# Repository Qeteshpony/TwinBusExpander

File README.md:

# TwinBusExpander

[Hardware Documentation](https://qeteshpony.github.io/TwinBusExpander)

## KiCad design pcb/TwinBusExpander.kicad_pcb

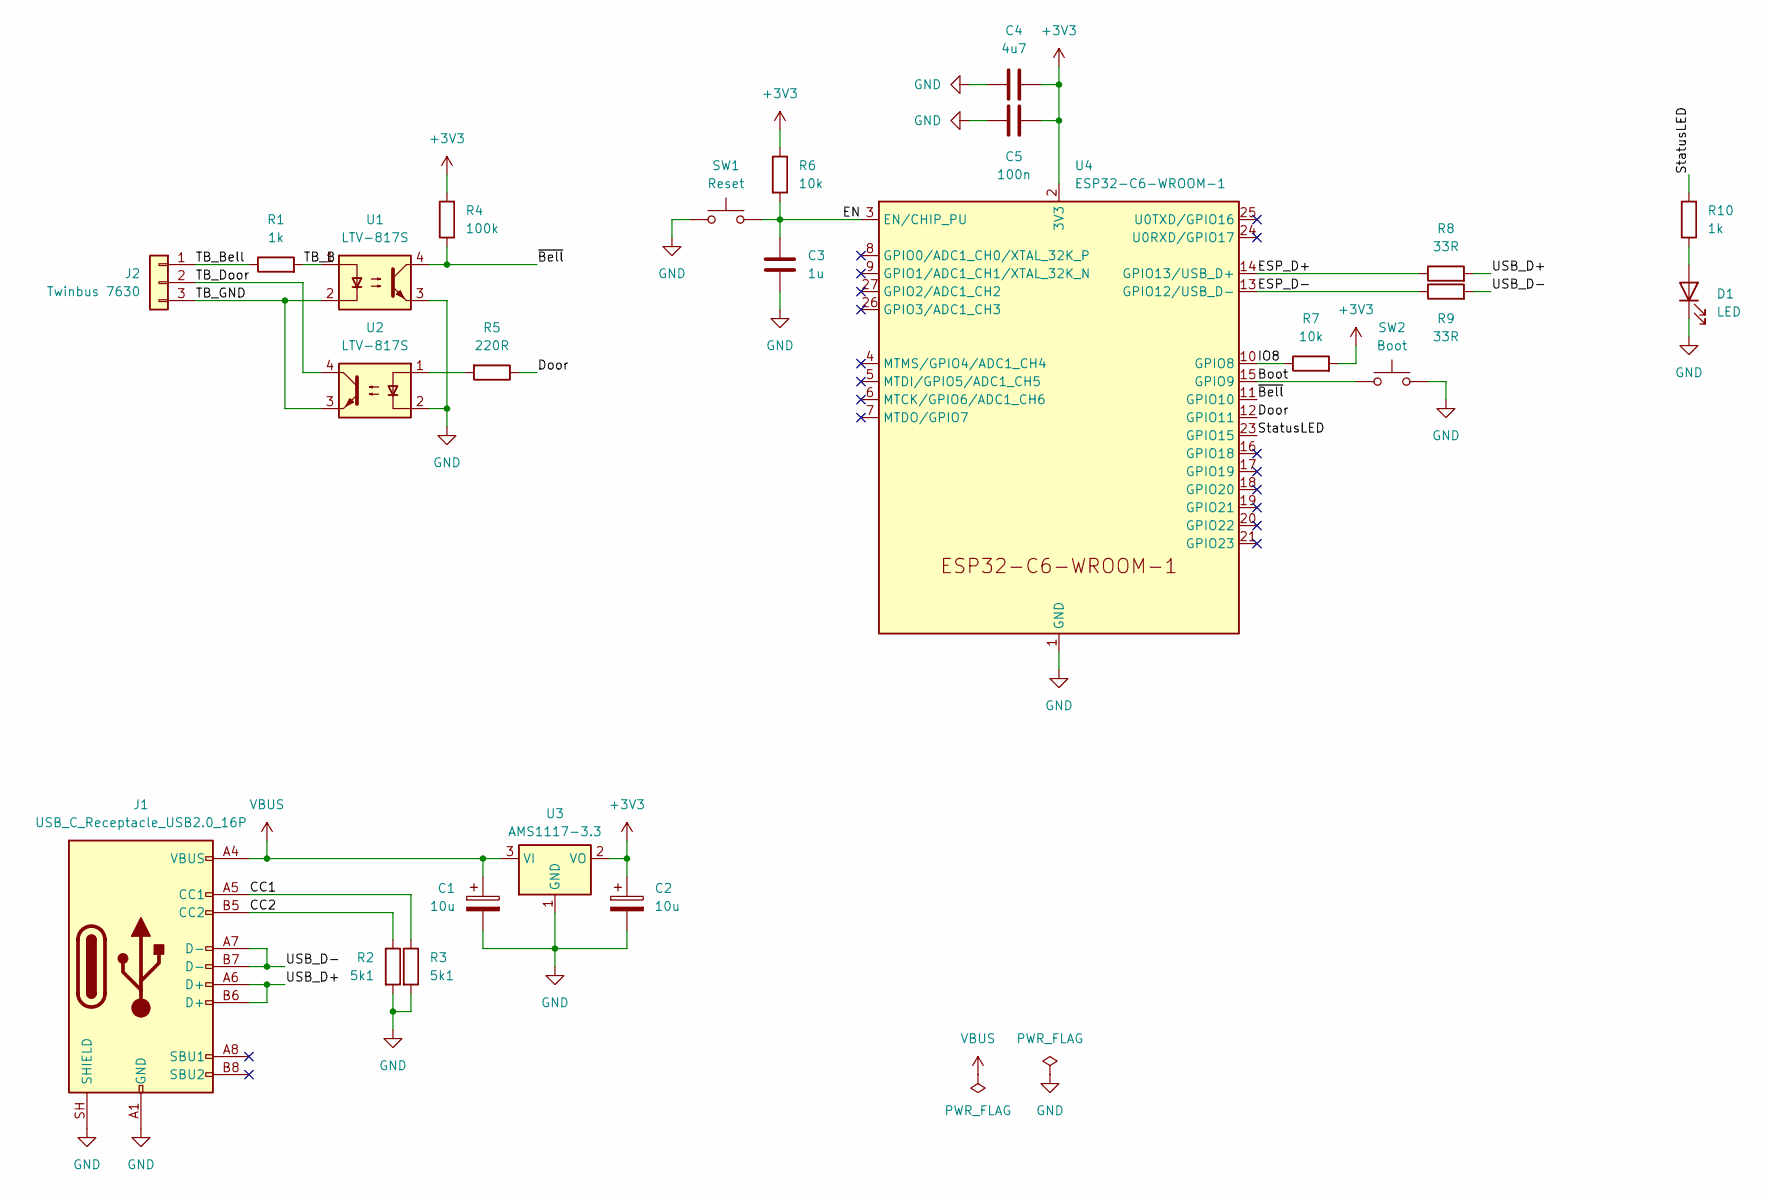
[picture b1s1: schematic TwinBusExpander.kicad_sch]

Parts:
C1, C2: 10u; CP_EIA-3216-18_Kemet-A; LCSC C7171
C3: 1u; C_0402_1005Metric; LCSC C52923
C4: 4u7; C_0402_1005Metric; LCSC C23733
C5: 100n; C_0402_1005Metric; LCSC C1525
D1: LED; LED_0603_1608Metric; LCSC C2286
J1: USB_C_Receptacle_USB2.0_16P; USB_C_Receptacle_GCT_USB4105-xx-A_16P_TopMnt_Horizontal; LCSC C393939
J2: Twinbus 7630; JST_PH_S3B-PH-K_1x03_P2.00mm_Horizontal; LCSC C157929
R1, R10: 1k; R_0402_1005Metric; LCSC C11702
R2, R3: 5k1; R_0402_1005Metric; LCSC C25905
R4: 100k; R_0402_1005Metric; LCSC C25741
R5: 220R; R_0402_1005Metric; LCSC C25091
R6, R7: 10k; R_0402_1005Metric; LCSC C25744
R8, R9: 33R; R_0402_1005Metric; LCSC C25105
SW1: Reset; SW_SPST_TS-1088-xR020; LCSC C720477
SW2: Boot; SW_SPST_TS-1088-xR020; LCSC C720477
U1, U2: LTV-817S; SMDIP-4_W9.53mm; LCSC C109227
U3: AMS1117-3.3; SOT-223-3_TabPin2; LCSC C6186
U4: ESP32-C6-WROOM-1

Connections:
+3V3: C2.1, C4.2, C5.2, R4.2, R6.1, R7.2, U3.2 (VO), U4.2 (3V3)
/Boot: SW2.1, U4.15 (GPIO9)
/CC1: J1.A5 (CC1), R3.1
/CC2: J1.B5 (CC2), R2.1
/Door: R5.1, U4.12 (GPIO11)
/EN: C3.1, R6.2, SW1.2, U4.3 (EN/CHIP_PU)
/ESP_D+: R8.1, U4.14 (GPIO13/USB_D+)
/ESP_D-: R9.1, U4.13 (GPIO12/USB_D-)
/IO8: R7.1, U4.10 (GPIO8)
/StatusLED: R10.2, U4.23 (GPIO15)
/TB_B: R1.2, U1.1
/TB_Bell: J2.1, R1.1
/TB_Door: J2.2, U2.4
/TB_GND: J2.3, U1.2, U2.3
/USB_D+: J1.A6 (D+), J1.B6 (D+), R8.2
/USB_D-: J1.A7 (D-), J1.B7 (D-), R9.2
/~Bell: R4.1, U1.4, U4.11 (GPIO10)
GND: C1.2, C2.2, C3.2, C4.1, C5.1, D1.1 (K), J1.A1 (GND), J1.A12 (GND), J1.B1 (GND), J1.B12 (GND), J1.SH (SHIELD), R2.2, R3.2, SW1.1, SW2.2, U1.3, U2.2, U3.1 (GND), U4.1 (GND), U4.28 (GND), U4.29 (GND)
unnamed: D1.2 (A), R10.1
unnamed: R5.2, U2.1
VBUS: C1.1, J1.A4 (VBUS), J1.A9 (VBUS), J1.B4 (VBUS), J1.B9 (VBUS), U3.3 (VI)

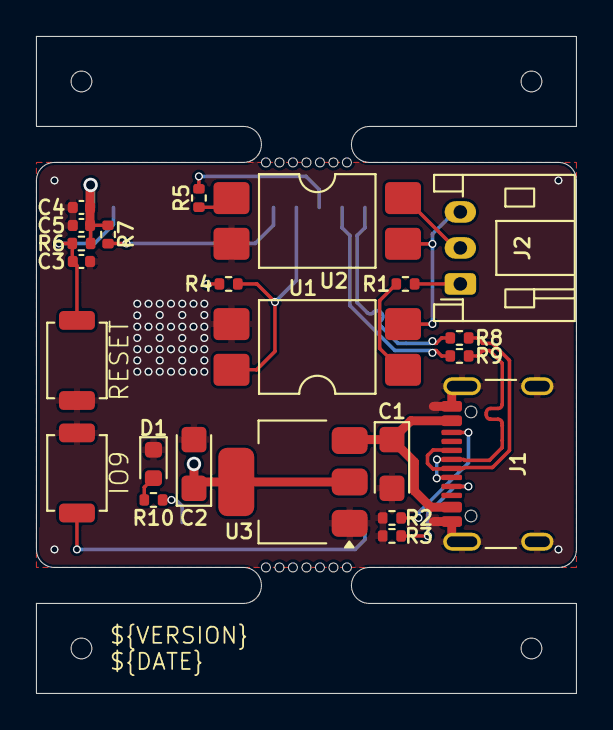
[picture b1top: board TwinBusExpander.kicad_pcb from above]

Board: 4 copper layers, 30.0 x 36.5 mm, 26 parts (1 on the bottom side), 21 nets.

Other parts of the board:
mouse-bite-2mm-slot, mouse-bite-2mm-slot#2: VAL**; mouse-bite-2x5mm-slot-onesided-v2
